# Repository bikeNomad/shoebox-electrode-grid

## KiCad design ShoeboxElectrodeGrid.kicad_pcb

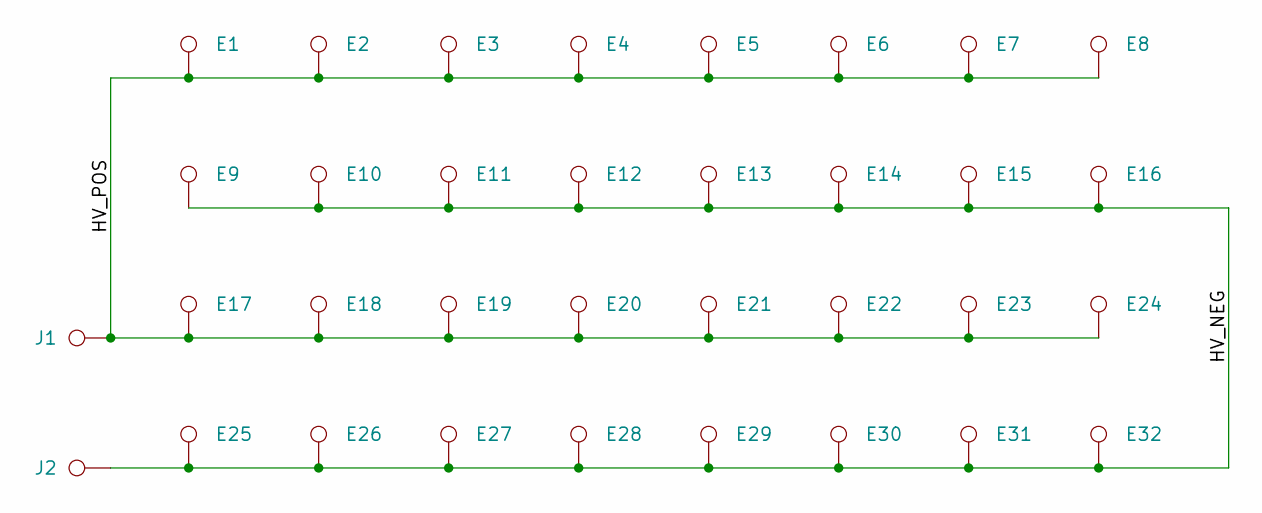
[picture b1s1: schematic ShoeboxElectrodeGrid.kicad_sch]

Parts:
E1, E2, E3, E4, E5, E6, E7, E8, E9, E10, E11, E12, E13, E14, E15, E16, E17, E18, E19, E20, E21, E22, E23, E24, E25, E26, E27, E28, E29, E30, E31, E32: TestPoint; TestPoint_THTPad_D2.0mm_Drill1.0mm
J1, J2: TestPoint; TestPoint_THTPad_D3.0mm_Drill1.5mm

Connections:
/HV_NEG: E9.1, E10.1, E11.1, E12.1, E13.1, E14.1, E15.1, E16.1, E25.1, E26.1, E27.1, E28.1, E29.1, E30.1, E31.1, E32.1, J2.1
/HV_POS: E1.1, E2.1, E3.1, E4.1, E5.1, E6.1, E7.1, E8.1, E17.1, E18.1, E19.1, E20.1, E21.1, E22.1, E23.1, E24.1, J1.1

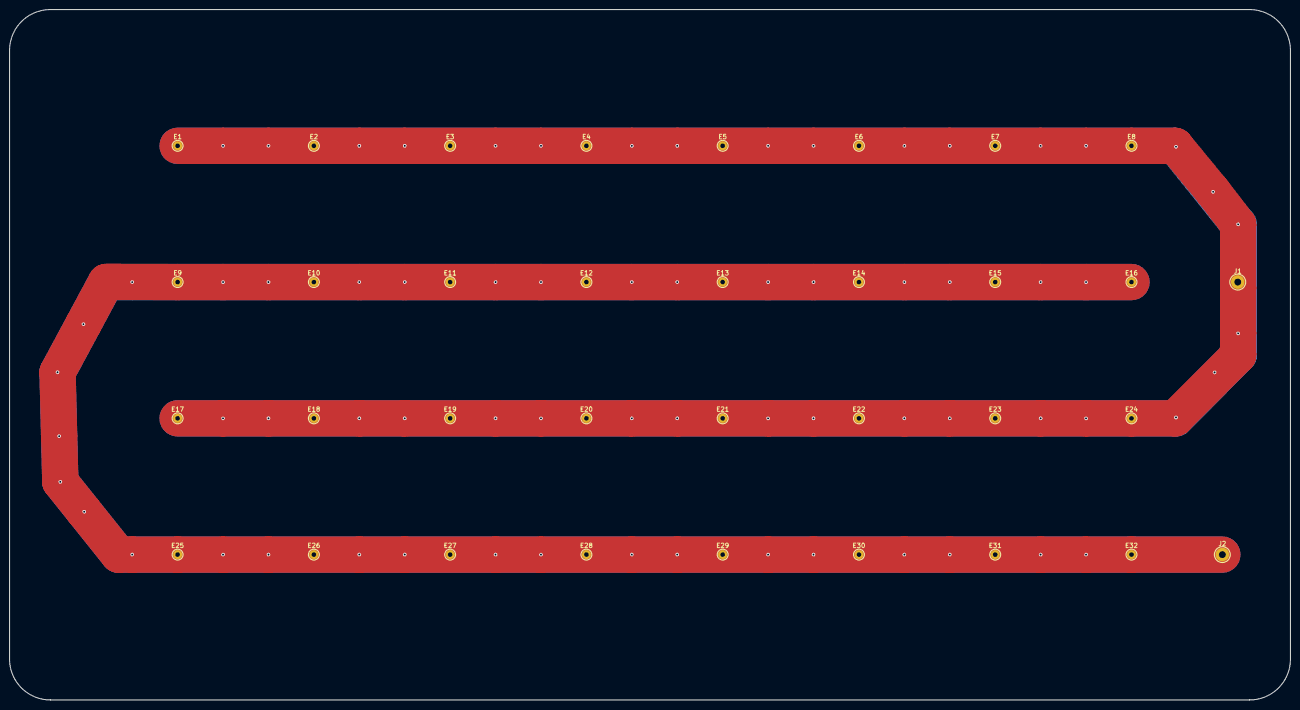
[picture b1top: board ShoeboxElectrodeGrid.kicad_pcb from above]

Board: 2 copper layers, 282.0 x 152.0 mm, 34 parts (0 on the bottom side), 2 nets.

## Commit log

2022-12-04 Initial commit, as sent to JLCPCB
2022-12-05 Added .gitignore
